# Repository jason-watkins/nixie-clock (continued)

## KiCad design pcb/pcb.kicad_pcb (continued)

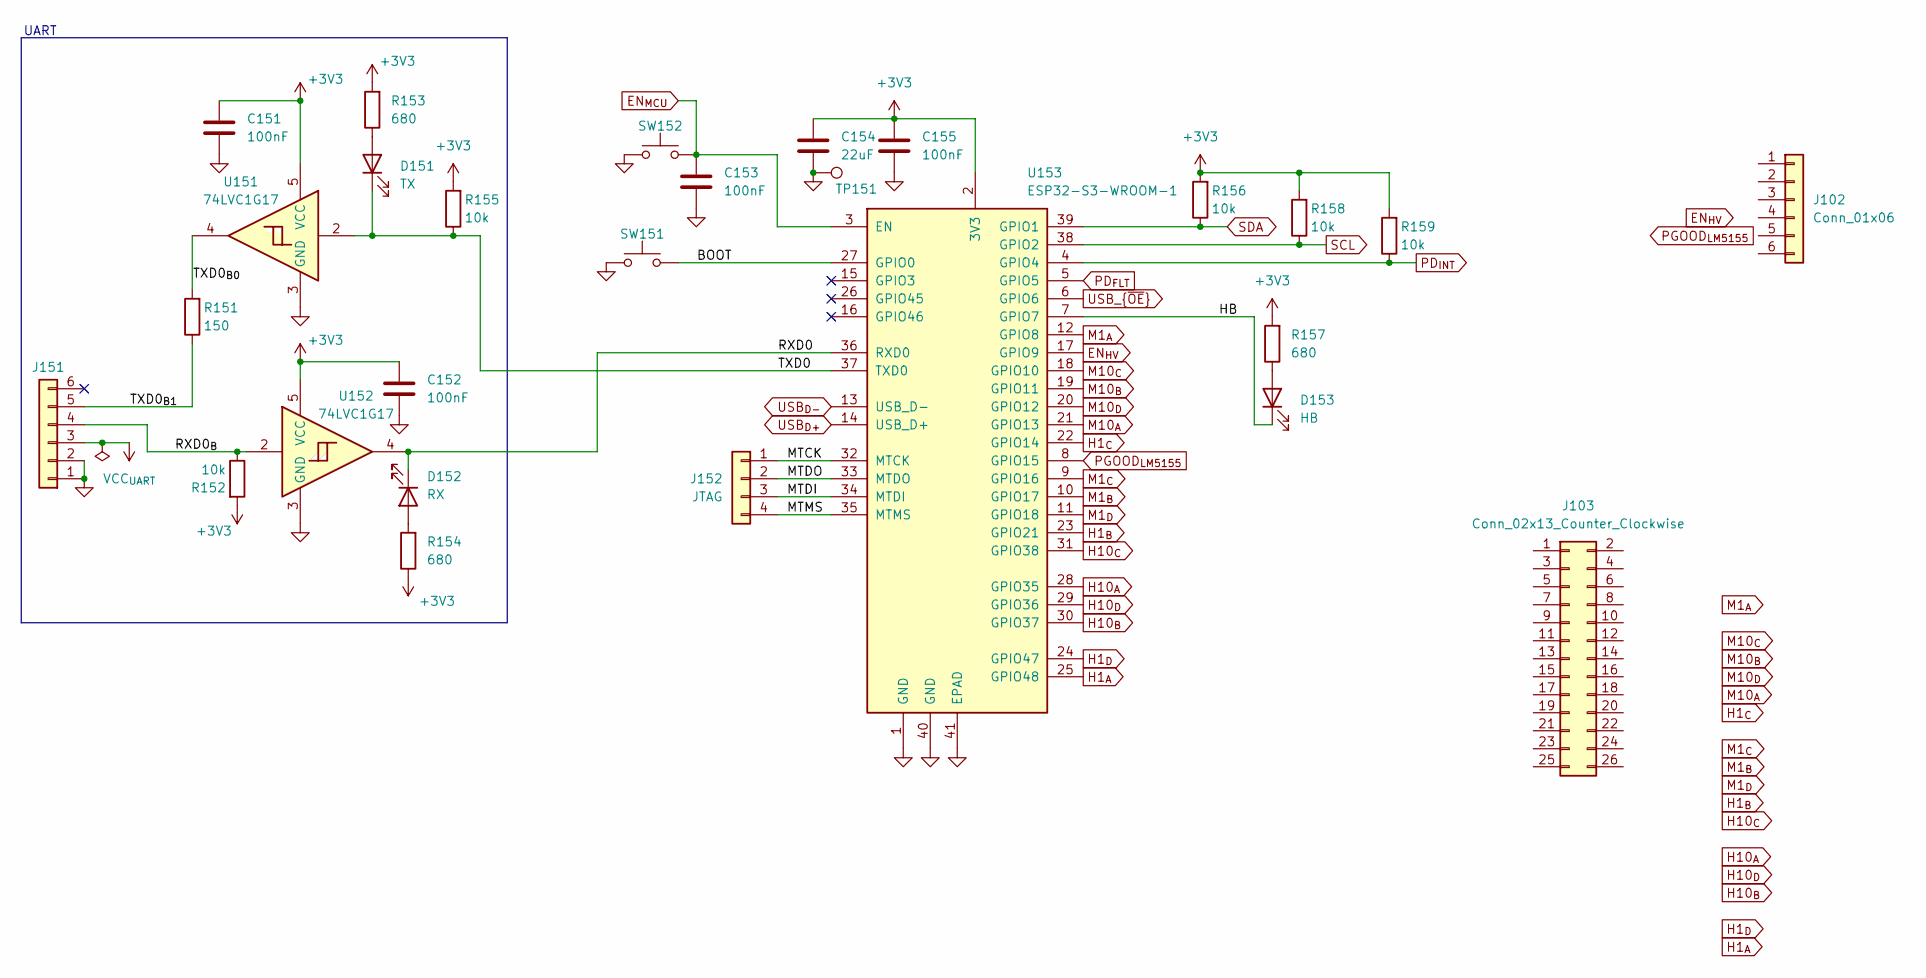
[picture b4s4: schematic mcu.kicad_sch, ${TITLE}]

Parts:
C151, C152, C153, C155: 100nF; C_0402_1005Metric; MFG Part No CL05B104KO5NNNC; LCSC C1525
C154: 22uF; C_0603_1608Metric; MFG Part No CL10A226MQ8NRNC; LCSC C59461
D151: TX; LED_0603_1608Metric; MFG Part No NCD0603Y2; LCSC C89811
D152: RX; LED_0603_1608Metric; MFG Part No NCD0603Y2; LCSC C89811
D153: HB; LED_0603_1608Metric; MFG Part No NCD0603Y2; LCSC C89811
J102: Conn_01x06; JST_XH_S6B-XH-A_1x06_P2.50mm_Horizontal
J103: Conn_02x13_Counter_Clockwise; IDC-Header_2x13_P2.54mm_Vertical
J151: UART; PinHeader_1x06_P2.54mm_Vertical
J152: JTAG; PinHeader_1x04_P2.54mm_Vertical
R151: 150; R_0402_1005Metric; MFG Part No 0402WGF1500TCE; LCSC C25082
R152, R155, R156, R158, R159: 10k; R_0402_1005Metric; MFG Part No 0402WGF1002TCE; LCSC C25744
R153, R154, R157: 680; R_0402_1005Metric; MFG Part No 0402WGF6800TCE; LCSC C25130
SW151: Boot; SW_Panasonic_EVQ_4.9x4.9mm; MFG Part No EVQ-PT9A15
SW152: Reset; SW_Panasonic_EVQ_4.9x4.9mm; MFG Part No EVQ-PT9A15
TP151: GND; TestPoint_Pad_D1.0mm
U151, U152: 74LVC1G17; SOT-23-5
U153: ESP32-S3-WROOM-1; MFG Part No ESP32-S3-WROOM-1-N8

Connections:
+3V3: C151.1, C152.1, C154.1, C155.1, R152.2, R153.2, R154.1, R155.2, R156.2, R157.2, R158.2, R159.2, U151.5 (VCC), U152.5 (VCC), U153.2 (3V3); also elsewhere on the board
/MCU/BOOT: SW151.2, U153.27 (GPIO0)
/MCU/HB: D153.1 (K), U153.7 (GPIO7)
/MCU/MTCK: J152.1, U153.32 (MTCK)
/MCU/MTDI: J152.3, U153.34 (MTDI)
/MCU/MTDO: J152.2, U153.33 (MTDO)
/MCU/MTMS: J152.4, U153.35 (MTMS)
/MCU/RXD0: D152.1 (K), U152.4, U153.36 (RXD0)
/MCU/RXD0_{B}: J151.4, R152.1, U152.2
/MCU/TXD0: D151.1 (K), R155.1, U151.2, U153.37 (TXD0)
/MCU/TXD0_{B0}: R151.2, U151.4
/MCU/TXD0_{B1}: J151.5, R151.1
EN_{HV}: U153.17 (GPIO9); also elsewhere on the board
EN_{MCU}: C153.1, SW152.2, U153.3 (EN); also elsewhere on the board
GND: C151.2, C152.2, C153.2, C154.2, C155.2, J151.1, J151.2, SW151.1, SW152.1, TP151.1, U151.3 (GND), U152.3 (GND), U153.1 (GND), U153.40 (GND), U153.41 (EPAD); also elsewhere on the board
H1_{A}: U153.25 (GPIO48); also elsewhere on the board
H1_{B}: U153.23 (GPIO21); also elsewhere on the board
H1_{C}: U153.22 (GPIO14); also elsewhere on the board
H1_{D}: U153.24 (GPIO47); also elsewhere on the board
H10_{A}: U153.28 (GPIO35); also elsewhere on the board
H10_{B}: U153.30 (GPIO37); also elsewhere on the board
H10_{C}: U153.31 (GPIO38); also elsewhere on the board
H10_{D}: U153.29 (GPIO36); also elsewhere on the board
M1_{A}: U153.12 (GPIO8); also elsewhere on the board
M1_{B}: U153.10 (GPIO17); also elsewhere on the board
M1_{C}: U153.9 (GPIO16); also elsewhere on the board
M1_{D}: U153.11 (GPIO18); also elsewhere on the board
M10_{A}: U153.21 (GPIO13); also elsewhere on the board
M10_{B}: U153.19 (GPIO11); also elsewhere on the board
M10_{C}: U153.18 (GPIO10); also elsewhere on the board
M10_{D}: U153.20 (GPIO12); also elsewhere on the board
unnamed: D151.2 (A), R153.1
unnamed: D152.2 (A), R154.2
unnamed: D153.2 (A), R157.1
PD_{FLT}: U153.5 (GPIO5); also elsewhere on the board
PD_{INT}: R159.1, U153.4 (GPIO4); also elsewhere on the board
PGOOD_{LM5155}: U153.8 (GPIO15); also elsewhere on the board
SCL: R158.1, U153.38 (GPIO2); also elsewhere on the board
SDA: R156.1, U153.39 (GPIO1); also elsewhere on the board
USB_{D+}: U153.14 (USB_D+); also elsewhere on the board
USB_{D-}: U153.13 (USB_D-); also elsewhere on the board
USB_{~OE}: U153.6 (GPIO6); also elsewhere on the board
VCC_{UART}: J151.3; also elsewhere on the board

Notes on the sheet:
UART

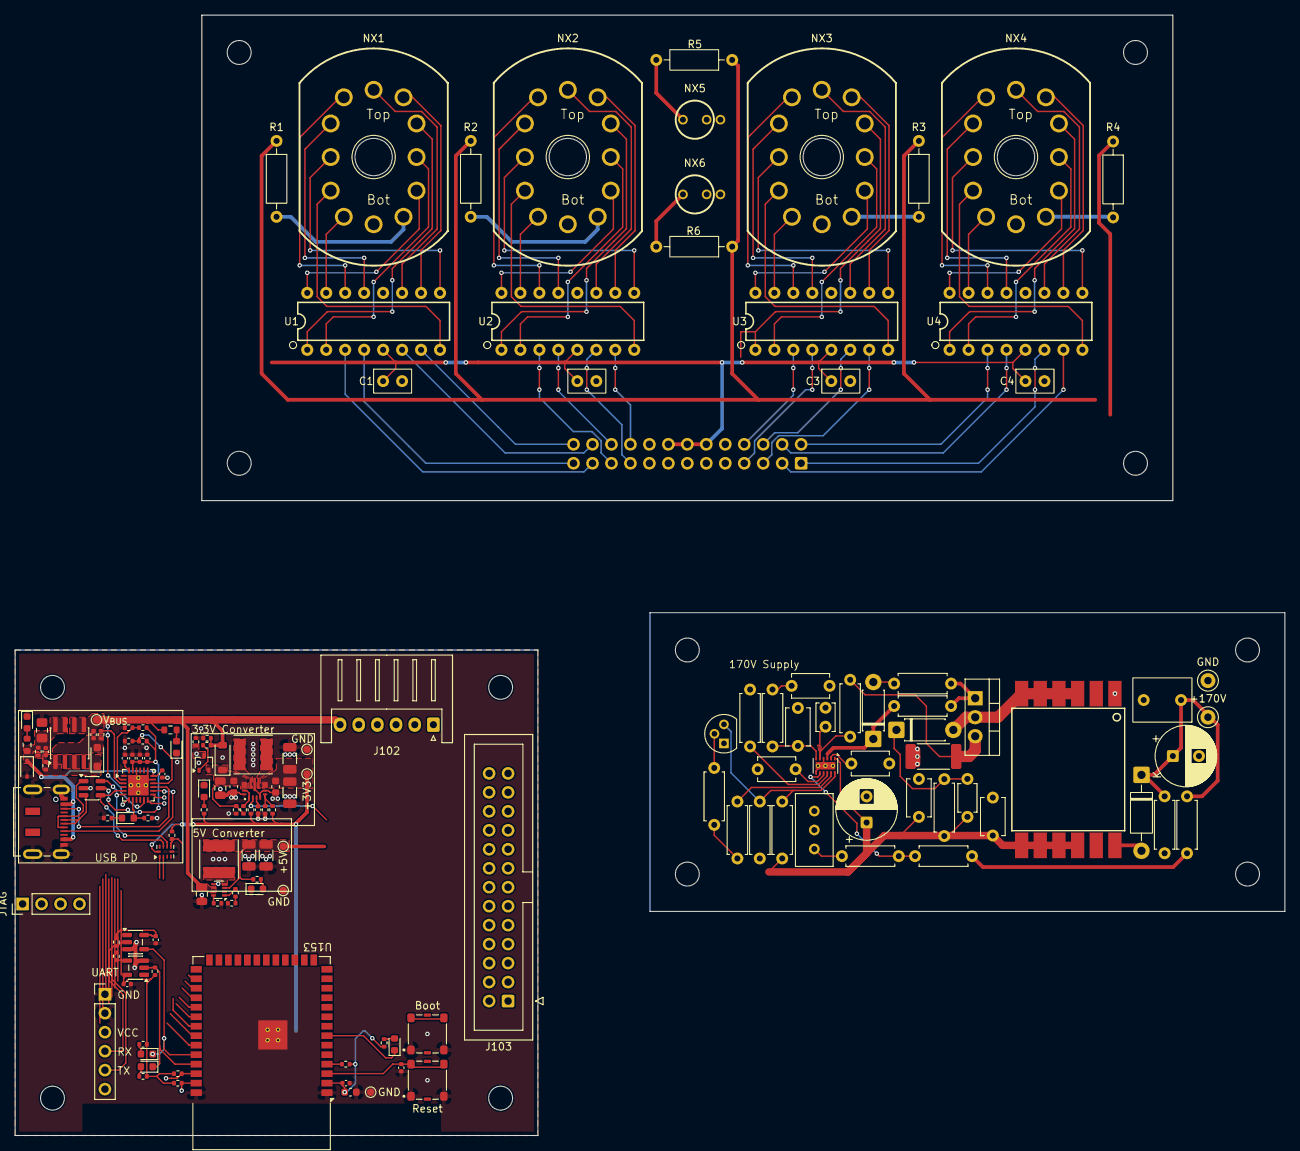
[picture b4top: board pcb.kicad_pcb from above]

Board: 2 copper layers, 170.0 x 150.0 mm, 161 parts (1 on the bottom side), 139 nets.

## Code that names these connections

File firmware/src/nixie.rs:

use crate::hv;
use crate::status::HvStatus;
use crate::time;
use chrono::DateTime;
use chrono::FixedOffset;
use chrono::Timelike;
use defmt::info;
use defmt::trace;
use defmt::warn;
use embassy_executor::Spawner;
use embassy_sync::watch::DynReceiver;
use embassy_time::Duration;
use embassy_time::Instant;
use embassy_time::Timer;
use esp_hal::gpio::Level;
use esp_hal::gpio::Output;
use esp_hal::gpio::OutputConfig;
use esp_hal::gpio::OutputPin;

/// Binds the board's GPIO assignments to the display.
#[macro_export]
macro_rules! nixie_pins {
    ($p:ident) => {
        $crate::nixie::ClockFace::new(
            $crate::nixie::Bcd::new($p.GPIO9, $p.GPIO13, $p.GPIO21, $p.GPIO11),
            $crate::nixie::Bcd::new($p.GPIO47, $p.GPIO12, $p.GPIO10, $p.GPIO14),
            $crate::nixie::Bcd::new($p.GPIO18, $p.GPIO7, $p.GPIO5, $p.GPIO16),
            $crate::nixie::Bcd::new($p.GPIO4, $p.GPIO15, $p.GPIO17, $p.GPIO6),
        )
    };
}

/// Represents a single BCD converter/tube output
pub struct Bcd<'a> {
    pins: [Output<'a>; 4], // [A, B, C, D]
}

impl<'a> Bcd<'a> {
    pub fn new(
        a: impl OutputPin + 'a,
        b: impl OutputPin + 'a,
        c: impl OutputPin + 'a,
        d: impl OutputPin + 'a,
    ) -> Bcd<'a> {
        let initial_level = Level::High;
        let config = OutputConfig::default();
        let a = Output::new(a, initial_level, config);
        let b = Output::new(b, initial_level, config);
        let c = Output::new(c, initial_level, config);
        let d = Output::new(d, initial_level, config);
        Bcd { pins: [a, b, c, d] }
    }

    pub fn write(&mut self, d: Option<u8>) {
        const BLANK: u8 = 0b00001111;
        let d = d
            .map(|d| {
                if d > 9 {
                    warn!("Writing out of range digit {}, display will be blank", d);
                    BLANK
                } else {
                    const DIGIT_TO_BCD: [u8; 10] = [6, 4, 5, 1, 0, 9, 8, 2, 3, 7];
                    DIGIT_TO_BCD[d as usize]
                }
            })
            .unwrap_or(BLANK);

        for i in 0..4 {
            let on = if (d >> i) & 1 == 1 {
                Level::High
            } else {
                Level::Low
            };
            self.pins[i].set_level(on);
        }
    }
}

const DEFAULT_DISPLAY: [Option<u8>; 4] = [None, None, None, None];

pub struct ClockFace<'a> {
    h10: Bcd<'a>,
    h1: Bcd<'a>,
    m10: Bcd<'a>,
    m1: Bcd<'a>,
    hv_status_rx: DynReceiver<'static, HvStatus>,
    hv_status: HvStatus,
    shown: [Option<u8>; 4],
}

impl<'a> ClockFace<'a> {
    pub fn new(h10: Bcd<'a>, h1: Bcd<'a>, m10: Bcd<'a>, m1: Bcd<'a>) -> ClockFace<'a> {
        ClockFace {
            h10,
            h1,
            m10,
            m1,
            hv_status_rx: hv::status_receiver(),
            hv_status: HvStatus::Off,
            shown: DEFAULT_DISPLAY,
        }
    }

    pub async fn write_digits(&mut self, digits: [Option<u8>; 4]) {
        self.m1.write(digits[3]);
        trace!("M1: {}", digits[3]);
        if self.shown[3] == None {
            Timer::after_millis(25).await;
        }
        self.m10.write(digits[2]);
        trace!("M10: {}", digits[2]);
        if self.shown[2] == None {
            Timer::after_millis(25).await;
        }
        self.h1.write(digits[1]);
        trace!("H1: {}", digits[1]);
        if self.shown[1] == None {
            Timer::after_millis(25).await;
        }
        self.h10.write(digits[0]);
        trace!("H10: {}", digits[0]);
        self.shown = digits;
    }

    pub async fn blank(&mut self) {
        self.write_digits(DEFAULT_DISPLAY).await;
    }

    pub async fn run(mut self) -> ! {
        loop {
            self.wait_for_hv().await;

            let now = time::local_now().map(digits).unwrap_or(DEFAULT_DISPLAY);
            if now != self.shown {
                let glyphs = now.map(|d| match d {
                    Some(d) => char::from_digit(d as u32, 10).unwrap_or('?'),
                    None => ' ',
                });
                info!("{}{}:{}{}", glyphs[0], glyphs[1], glyphs[2], glyphs[3]);
                self.write_digits(now).await;
            }

            // Try to keep clock updates precise. On the normal path, tick slowly to just before the
            // next update, then busy wait. The slow ticks rather than a single sleep bound how long
            // it takes us to pick up on an NTP update. On all other paths, degrade gracefully in
            // ways that don't hog the core too badly.
            let remaining = Self::until_next_minute();
            const GUARD: Duration = Duration::from_millis(1);
            let remaining = remaining
                .checked_sub(GUARD)
                .unwrap_or_default()
                .max(Duration::from_micros(100))
                .min(Duration::from_secs(5));
            Timer::after(remaining).await;

            let remaining = Self::until_next_minute();
            if remaining <= GUARD {
                let deadline = Instant::now() + remaining;
                while Instant::now() < deadline {
                    core::hint::spin_loop();
                }
            }
        }
    }

    fn until_next_minute() -> Duration {
        let Some(now) = time::local_now() else {
            const DEFAULT_TICK: Duration = Duration::from_secs(5);
            return DEFAULT_TICK;
        };

        const ONE_MINUTE: Duration = Duration::from_secs(60);
        let current_minute_fraction = Duration::from_secs(now.second() as u64)
            + Duration::from_micros(now.timestamp_subsec_micros() as u64);
        ONE_MINUTE
            .checked_sub(current_minute_fraction)
            .unwrap_or_default()
    }

    async fn wait_for_hv(&mut self) {
        let last_status = self.hv_status;
        self.hv_status = self.hv_status_rx.get().await;
        if self.status_good(last_status).await {
            return;
        }

        loop {
            let last_status = self.hv_status;
            self.hv_status = self.hv_status_rx.changed().await;
            if self.status_good(last_status).await {
                return;
            }
        }
    }

    async fn status_good(&mut self, last_status: HvStatus) -> bool {
        const RAIL_STABILIZATION_TIME: Duration = Duration::from_millis(50);
        match self.hv_status {
            HvStatus::Off => {
                self.blank().await;
                info!("Clock detected HV rail turn off. Blanking display");
                false
            }
            HvStatus::Starting => false,
            HvStatus::Up => {
                if last_status == HvStatus::Up {
                    // Previously up, so we've already waited for the rail to stabilize, and still up so we can
                    // continue operation without delay.
                    true
                } else {
                    info!(
                        "HV rail up, clock waiting {}ms to give it time to stabilize",
                        RAIL_STABILIZATION_TIME.as_millis()
                    );
                    Timer::after(RAIL_STABILIZATION_TIME).await; // Give the rail time to stabilize
                    self.hv_status = self.hv_status_rx.get().await;
                    if self.hv_status == HvStatus::Up {
                        info!("Clock wait complete. Resuming normal operation");
                        true
                    } else {
                        false
                    }
                }
            }
            HvStatus::Failed => false,
        }
    }
}

fn digits(t: DateTime<FixedOffset>) -> [Option<u8>; 4] {
    let hour = t.hour();
    let minute = t.minute();

    let h10 = (hour / 10) as u8;
    let h1 = (hour % 10) as u8;
    let m10 = (minute / 10) as u8;
    let m1 = (minute % 10) as u8;

    [Some(h10), Some(h1), Some(m10), Some(m1)]
}

pub fn init(clock_face: ClockFace<'static>, spawner: &Spawner) {
    let clock_token = update_clock(clock_face).expect("Failed to create clock task token");

    spawner.spawn(clock_token);
    info!("Clock initialized");
}

#[embassy_executor::task]
async fn update_clock(mut clock_face: ClockFace<'static>) -> ! {
    clock_face.blank().await;
    clock_face.run().await;
}
